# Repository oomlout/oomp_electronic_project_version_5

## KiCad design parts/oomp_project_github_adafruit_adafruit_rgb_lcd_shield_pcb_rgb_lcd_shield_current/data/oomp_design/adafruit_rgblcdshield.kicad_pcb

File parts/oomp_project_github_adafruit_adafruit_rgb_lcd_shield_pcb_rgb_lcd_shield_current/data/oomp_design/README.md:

# OOMP KiCad design copy

Open `adafruit_rgblcdshield.kicad_pro` (or the `.kicad_pcb` / `.kicad_sch`) in KiCad. Local OOMP libraries are under `libraries/`. Original inputs are preserved in [../original/](../original/).

Only verified unchanged installed KiCad defaults were renamed. Modified, custom, unmatched and unavailable items remain unchanged. Soldering variants are never swapped during conversion. Existing pad coordinates, nets and UUIDs are preserved.

See [conversion_report.yaml](conversion_report.yaml) for every conversion and skip. Copy this directory before editing; regeneration refuses to overwrite edited design files.

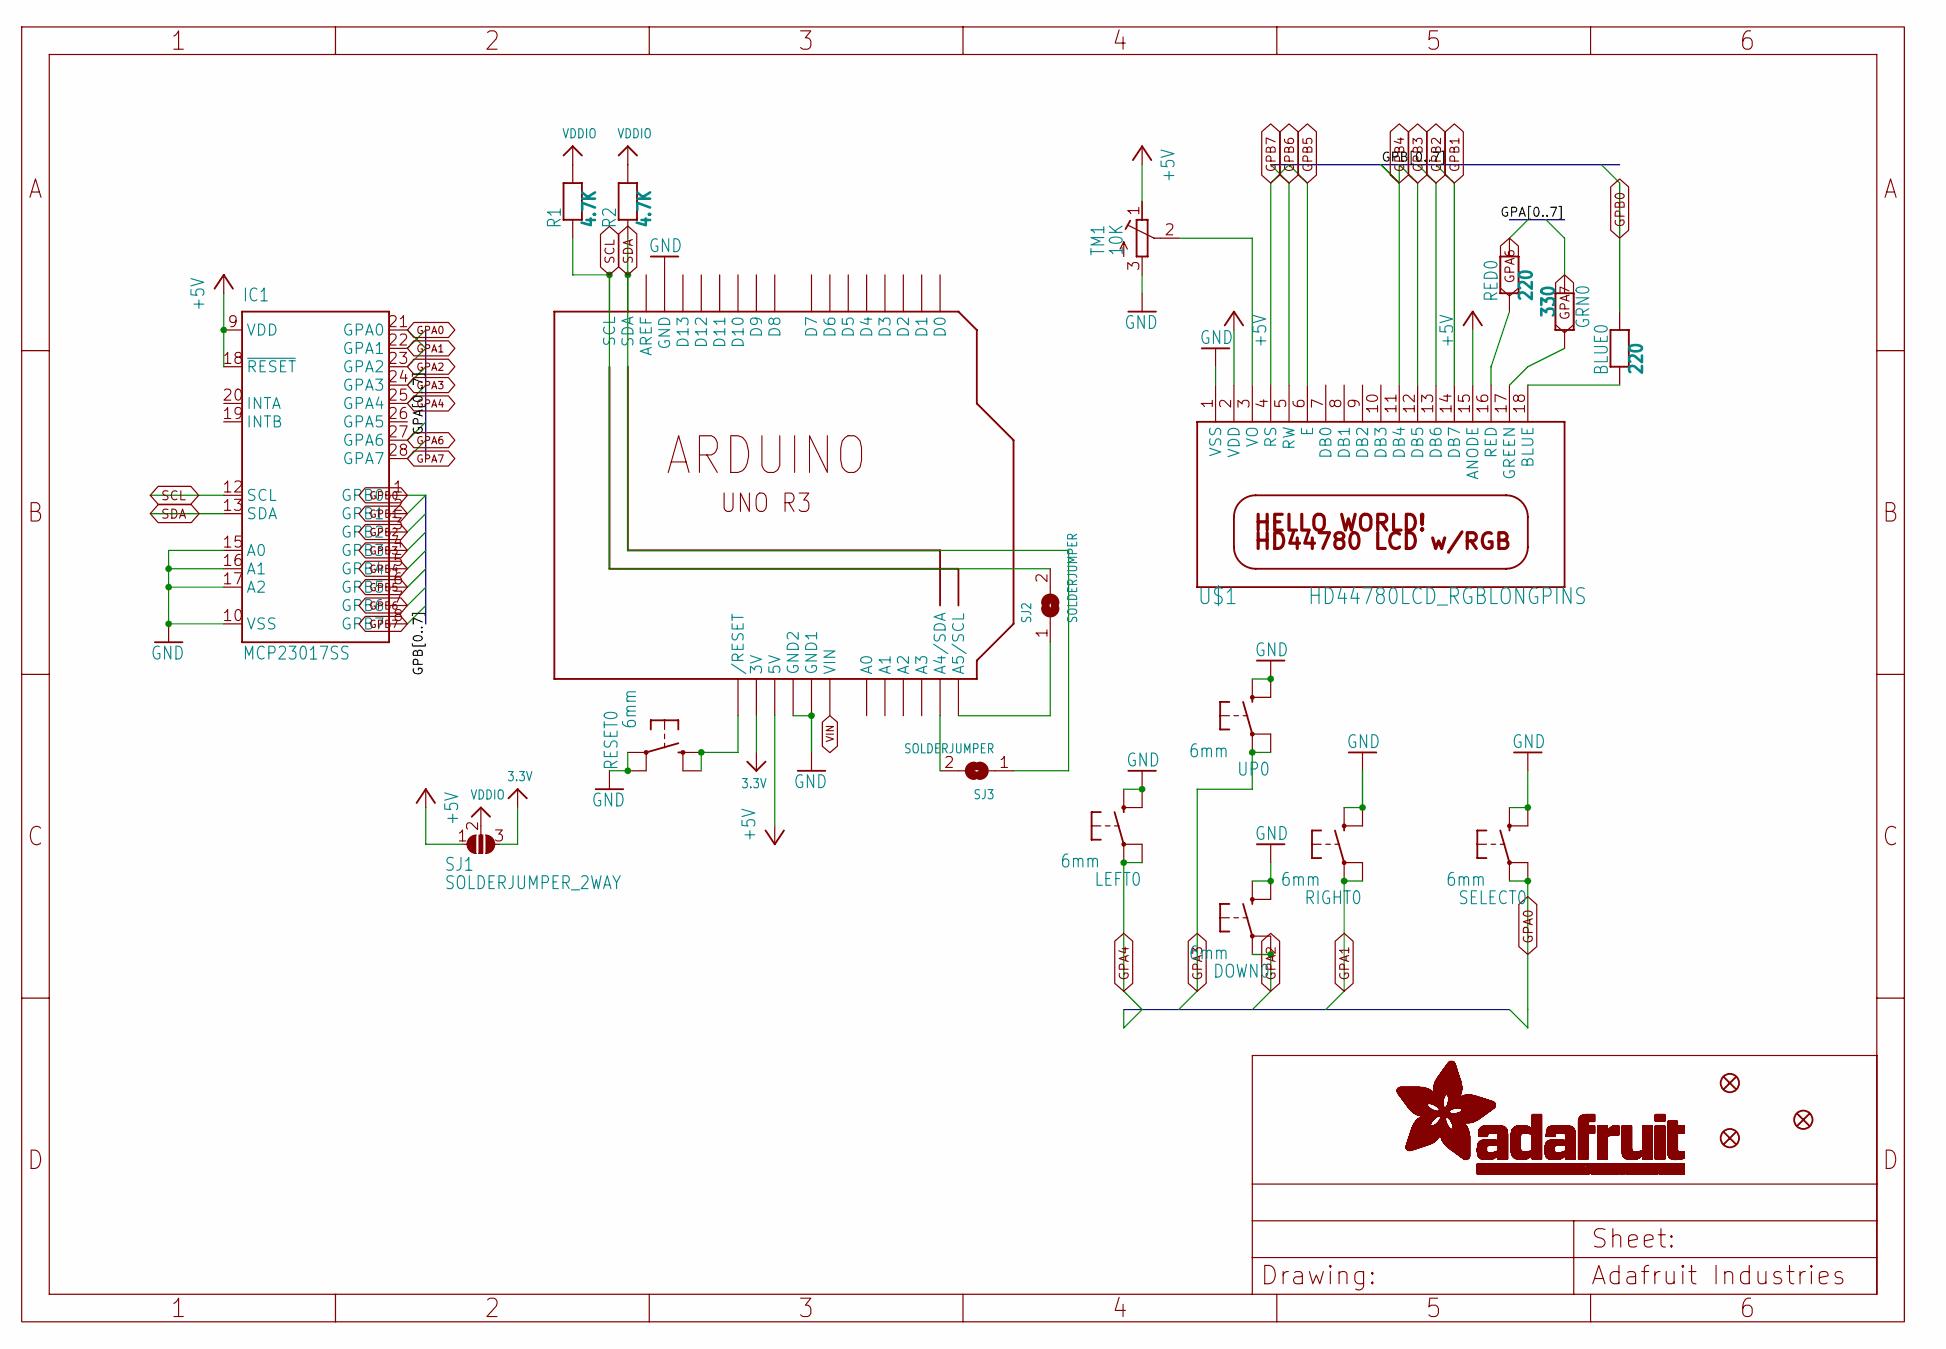
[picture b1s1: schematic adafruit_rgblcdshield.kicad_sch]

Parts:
BLUE0: 220; 0805-NO
DOWN0: 6mm; 6MMX6MM_TACTILE_SMT
FID1, FID2, FID3: FIDUCIAL_1MM
GRN0: 330; 0805-NO
IC1: MCP23017SS; SSOP28
LEFT0: 6mm; 6MMX6MM_TACTILE_SMT
R1, R2: 4.7K; 0805-NO
RED0: 220; 0805-NO
RESET0: 6mm; 6MMX6MM_TACTILE_SMT
RIGHT0: 6mm; 6MMX6MM_TACTILE_SMT
SELECT0: 6mm; 6MMX6MM_TACTILE_SMT
SJ1: SOLDERJUMPER_2WAY; SOLDERJUMPER_2WAY_OPEN_NOPASTE
SJ2, SJ3: SOLDERJUMPER; SOLDERJUMPER_ARROW_NOPASTE
TM1: 10K; RTRIM3314J
U1: ARDUINOR3-NOIOREF-NOTEXT; ARDUINOR3-NOTEXT-NOIOREF
U$1: HD44780LCD_RGBLONGPINS; LCD1602-RGB
UP0: 6mm; 6MMX6MM_TACTILE_SMT

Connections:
3.3V: SJ1.3, U1.3V
+5V: IC1.9 (VDD), IC1.18 (~RESET), SJ1.1, TM1.1 (E), U1.5V, U$1.2 (VDD), U$1.15 (ANODE)
GND: DOWN0.B (S), DOWN0.B' (S1), IC1.10 (VSS), IC1.15 (A0), IC1.16 (A1), IC1.17 (A2), LEFT0.B (S), LEFT0.B' (S1), RESET0.A, RESET0.A' (P1), RIGHT0.B (S), RIGHT0.B' (S1), SELECT0.B (S), SELECT0.B' (S1), TM1.3 (A), U1.GND, U1.GND1, U1.GND2, U$1.1 (VSS), UP0.B (S), UP0.B' (S1)
GPA0: IC1.21 (GPA0), SELECT0.A, SELECT0.A' (P1)
GPA1: IC1.22 (GPA1), RIGHT0.A, RIGHT0.A' (P1)
GPA2: DOWN0.A, DOWN0.A' (P1), IC1.23 (GPA2)
GPA3: IC1.24 (GPA3), UP0.A, UP0.A' (P1)
GPA4: IC1.25 (GPA4), LEFT0.A, LEFT0.A' (P1)
GPA6: IC1.27 (GPA6), RED0.2
GPA7: GRN0.1, IC1.28 (GPA7)
GPB0: BLUE0.2, IC1.1 (GPB0)
GPB1: IC1.2 (GPB1), U$1.14 (DB7)
GPB2: IC1.3 (GPB2), U$1.13 (DB6)
GPB3: IC1.4 (GPB3), U$1.12 (DB5)
GPB4: IC1.5 (GPB4), U$1.11 (DB4)
GPB5: IC1.6 (GPB5), U$1.6 (E)
GPB6: IC1.7 (GPB6), U$1.5 (RW)
GPB7: IC1.8 (GPB7), U$1.4 (RS)
unnamed: BLUE0.1, U$1.18 (BLUE)
unnamed: GRN0.2, U$1.17 (GREEN)
unnamed: RED0.1, U$1.16 (RED)
unnamed: TM1.2 (S), U$1.3 (VO)
unnamed: SJ3.2, U1.A4 (A4/SDA)
unnamed: SJ2.1, U1.A5 (A5/SCL)
RESET: RESET0.B (S), RESET0.B' (S1), U1.RESET (/RESET)
SCL: IC1.12 (SCL), R1.1, SJ2.2, U1.SCL
SDA: IC1.13 (SDA), R2.1, SJ3.1, U1.SDA
VDDIO: R1.2, R2.2, SJ1.2
VIN: U1.VIN

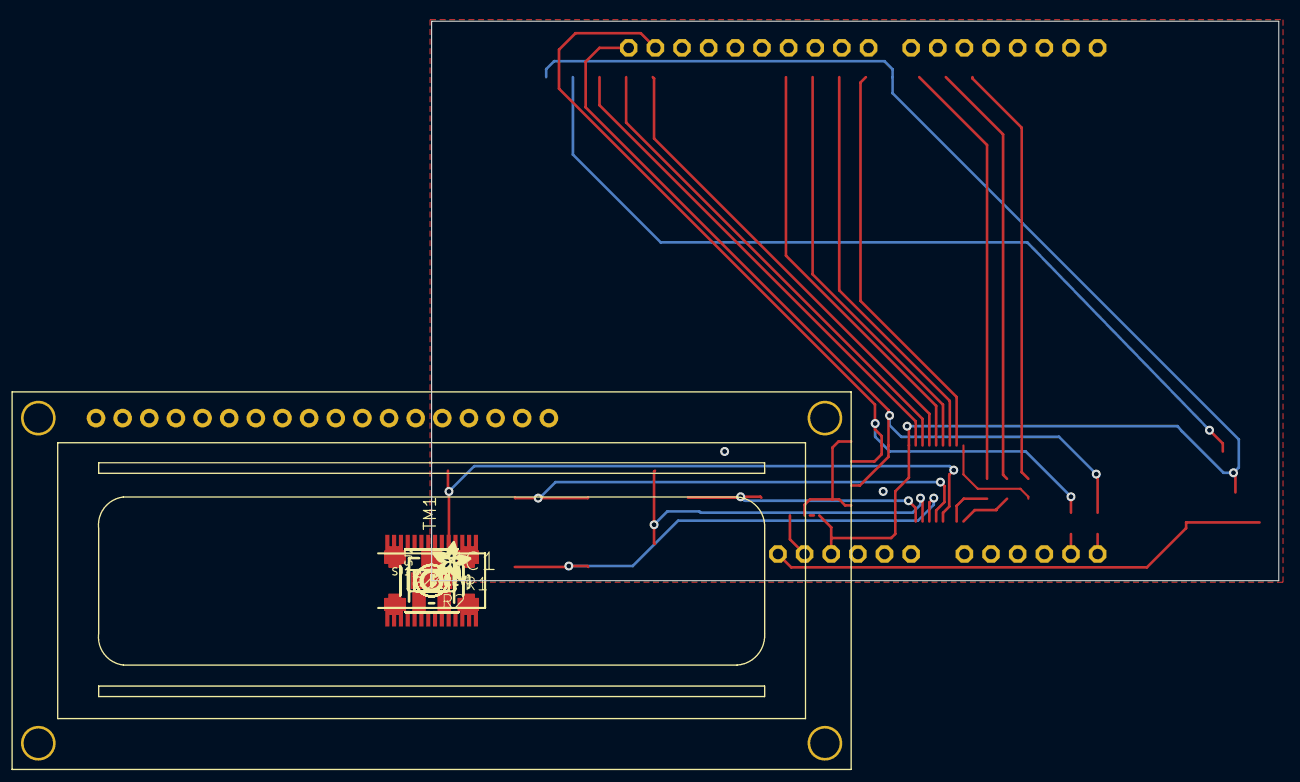
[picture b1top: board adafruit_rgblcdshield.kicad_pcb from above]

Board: 16 copper layers, 80.8 x 53.3 mm, 38 parts (0 on the bottom side), 28 nets.

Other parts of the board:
E$1: PCBFEAT-REV-040
PLABEL1: PLABEL1
PLABEL2: PLABEL2
PLABEL3: PLABEL3
PLABEL4: PLABEL4
PLABEL5: PLABEL5
PLABEL6: PLABEL6
PLABEL7: PLABEL7
PLABEL8: PLABEL8
PLABEL9: PLABEL9
PLABEL10: PLABEL10
PLABEL11: PLABEL11
PLABEL12: PLABEL12
PLABEL13: PLABEL13
PLABEL14: PLABEL14
PLABEL15: PLABEL15
U$4: ADAFRUIT_3.5MM

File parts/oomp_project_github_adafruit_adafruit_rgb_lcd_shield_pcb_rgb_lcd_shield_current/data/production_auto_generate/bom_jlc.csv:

Comment,Designator,Footprint,LCSC Part #
,U$4,adafruit_rgblcdshield-import-fps:ADAFRUIT_3.5MM,
,E$1,adafruit_rgblcdshield-import-fps:PCBFEAT-REV-040,
,PLABEL1,adafruit_rgblcdshield-import-fps:PLABEL1,
,PLABEL10,adafruit_rgblcdshield-import-fps:PLABEL10,
,PLABEL11,adafruit_rgblcdshield-import-fps:PLABEL11,
,PLABEL12,adafruit_rgblcdshield-import-fps:PLABEL12,
,PLABEL13,adafruit_rgblcdshield-import-fps:PLABEL13,
,PLABEL14,adafruit_rgblcdshield-import-fps:PLABEL14,
,PLABEL15,adafruit_rgblcdshield-import-fps:PLABEL15,
,PLABEL2,adafruit_rgblcdshield-import-fps:PLABEL2,
,PLABEL3,adafruit_rgblcdshield-import-fps:PLABEL3,
,PLABEL4,adafruit_rgblcdshield-import-fps:PLABEL4,
,PLABEL5,adafruit_rgblcdshield-import-fps:PLABEL5,
,PLABEL6,adafruit_rgblcdshield-import-fps:PLABEL6,
,PLABEL7,adafruit_rgblcdshield-import-fps:PLABEL7,
,PLABEL8,adafruit_rgblcdshield-import-fps:PLABEL8,
,PLABEL9,adafruit_rgblcdshield-import-fps:PLABEL9,
10K,TM1,adafruit_rgblcdshield-import-fps:RTRIM3314J,
220,BLUE0,adafruit_rgblcdshield-import-fps:0805-NO,
220,RED0,adafruit_rgblcdshield-import-fps:0805-NO,C2933369
330,GRN0,adafruit_rgblcdshield-import-fps:0805-NO,
4.7K,"R1,R2",adafruit_rgblcdshield-import-fps:0805-NO,C2907264
6mm,"DOWN0,LEFT0,RESET0,RIGHT0,SELECT0,UP0",adafruit_rgblcdshield-import-fps:6MMX6MM_TACTILE_SMT,
ARDUINOR3-NOIOREF-NOTEXT,U1,adafruit_rgblcdshield-import-fps:ARDUINOR3-NOTEXT-NOIOREF,
HD44780LCD_RGBLONGPINS,U$1,adafruit_rgblcdshield-import-fps:LCD1602-RGB,
MCP23017SS,IC1,adafruit_rgblcdshield-import-fps:SSOP28,

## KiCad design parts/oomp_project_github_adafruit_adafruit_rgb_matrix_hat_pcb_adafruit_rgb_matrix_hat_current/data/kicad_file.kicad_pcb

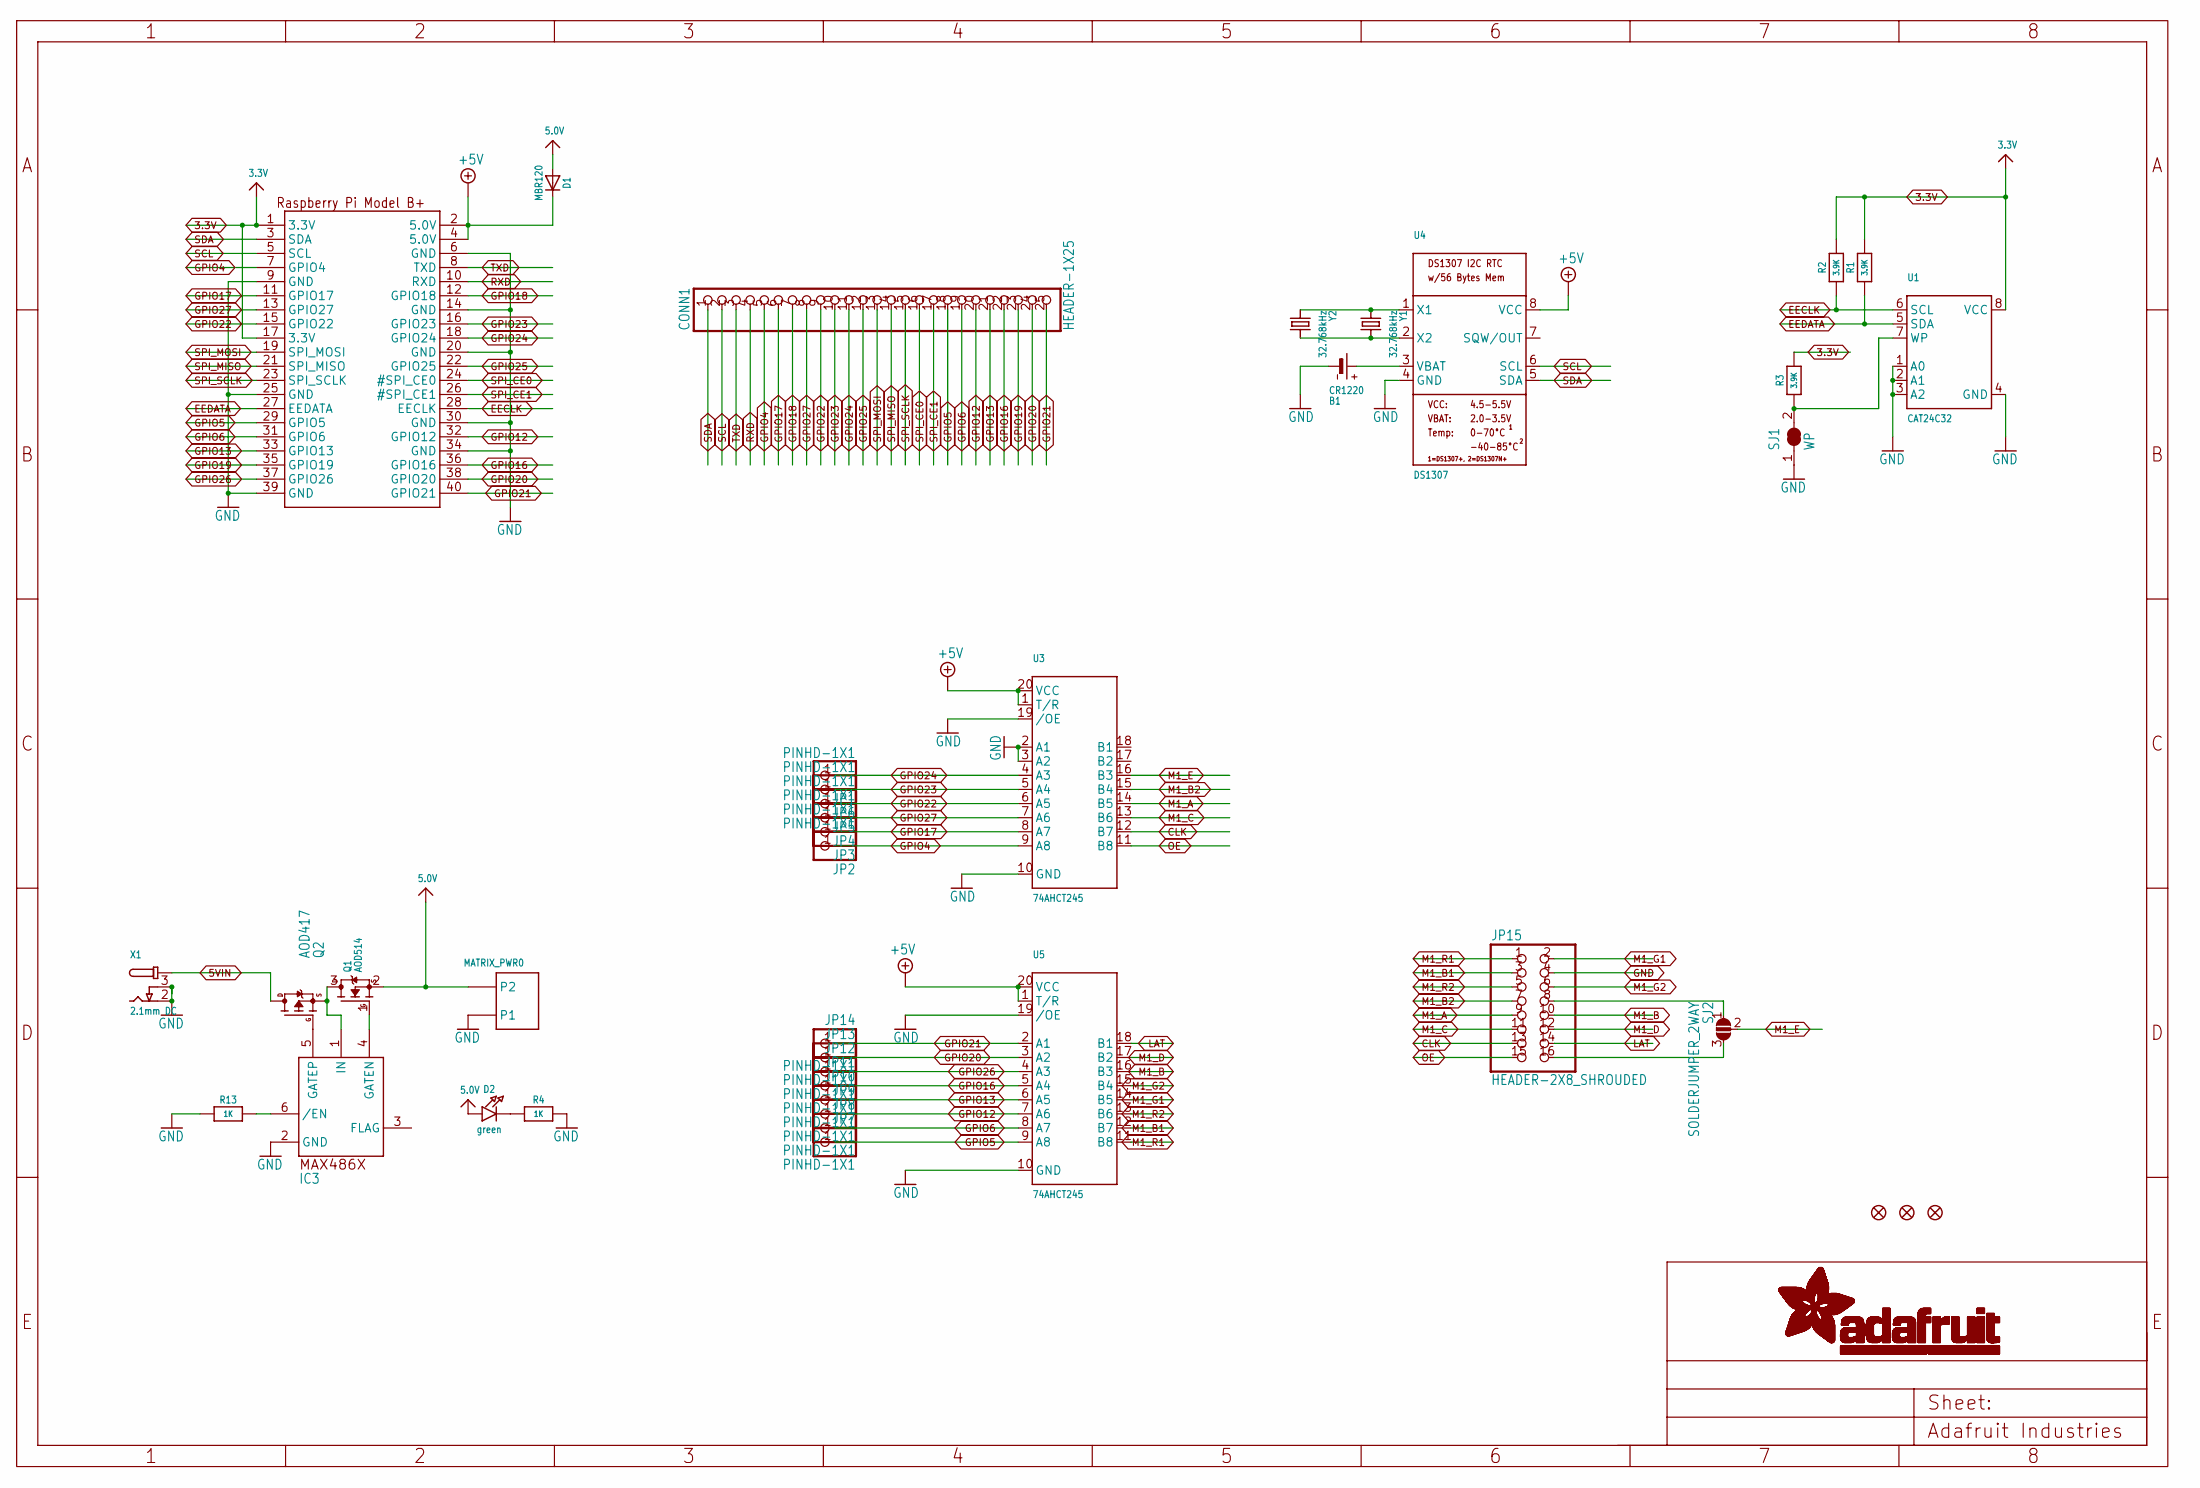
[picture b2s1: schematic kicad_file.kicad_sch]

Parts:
B1: CR1220
CONN1: HEADER-1X25; 1X25_ROUND_70MIL
D1: MBR120; SOD-123
D2: green; CHIPLED_0805_NOOUTLINE
FID1, FID2, FID3: FIDUCIAL_1MM
IC3: MAX4866T; SOT23-6
JP1, JP2, JP3, JP4, JP5, JP6, JP7, JP8, JP9, JP10, JP11, JP12, JP13, JP14: PINHD-1X1; 1X01
JP15: HEADER-2X8_SHROUDED; 2X08_SHROUDED
MATRIX_PWR0: PINHEAD; TERMBLOCK508
Q1: AOD514; TO252
Q2: AOD417; TO252
R1, R2, R3: 3.9K; 0805-NO
R4, R13: 1K; 0805-NO
RPI1: RASPBERRYPI_BPLUS_HATSLOTS; PI_HAT_SLOTS
SJ1: WP; SOLDERJUMPER_CLOSEDWIRE
SJ2: SOLDERJUMPER_2WAY; SOLDERJUMPER_2WAY_OPEN_NOPASTE
U1: CAT24C32; SOIC8_150MIL
U3, U5: 74AHCT245; TSSOP20
U4: DS1307; SOIC8_150MIL
X1: 2.1mm DC; DCJACK_2MM_SMT
Y1: 32.768kHz; CRYSTAL_8X3.8
Y2: 32.768kHz; XTAL3215

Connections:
3.3V: R1.2, R2.2, R3.2, RPI1.1 (3.3V), RPI1.17 (3.3V), U1.8 (VCC)
5.0V: D1.A, D2.A, MATRIX_PWR0.P$4 (P2), Q1.2 (S)
5VIN: Q2.3 (D), X1.1 (PWR), X1.1' (PWR)
+5V: D1.C, RPI1.2 (5.0V), RPI1.4 (5.0V), U3.1 (T/R), U3.20 (VCC), U4.8 (VCC), U5.1 (T/R), U5.20 (VCC)
CLK: JP15.13, U3.12 (B7)
EECLK: R2.1, RPI1.28 (EECLK), U1.6 (SCL)
EEDATA: R1.1, RPI1.27 (EEDATA), U1.5 (SDA)
GND: B1.-, IC3.2 (GND), JP15.4, MATRIX_PWR0.P$3 (P1), R4.2, R13.1, RPI1.6 (GND), RPI1.9 (GND), RPI1.14 (GND), RPI1.20 (GND), RPI1.25 (GND), RPI1.30 (GND), RPI1.34 (GND), RPI1.39 (GND), SJ1.1, U1.1 (A0), U1.2 (A1), U1.3 (A2), U1.4 (GND), U3.2 (A1), U3.3 (A2), U3.10 (GND), U3.19 (/OE), U4.4 (GND), U5.10 (GND), U5.19 (/OE), X1.2 (GND), X1.3 (GNDBREAK)
GPIO4: CONN1.5, JP2.1, RPI1.7 (GPIO4), U3.9 (A8)
GPIO5: CONN1.18, JP7.1, RPI1.29 (GPIO5), U5.9 (A8)
GPIO6: CONN1.19, JP8.1, RPI1.31 (GPIO6), U5.8 (A7)
GPIO12: CONN1.20, JP9.1, RPI1.32 (GPIO12), U5.7 (A6)
GPIO13: CONN1.21, JP10.1, RPI1.33 (GPIO13), U5.6 (A5)
GPIO16: CONN1.22, JP11.1, RPI1.36 (GPIO16), U5.5 (A4)
GPIO17: CONN1.6, JP3.1, RPI1.11 (GPIO17), U3.8 (A7)
GPIO18: CONN1.7, RPI1.12 (GPIO18)
GPIO19: CONN1.23, RPI1.35 (GPIO19)
GPIO20: CONN1.24, JP13.1, RPI1.38 (GPIO20), U5.3 (A2)
GPIO21: CONN1.25, JP14.1, RPI1.40 (GPIO21), U5.2 (A1)
GPIO22: CONN1.9, JP5.1, RPI1.15 (GPIO22), U3.6 (A5)
GPIO23: CONN1.10, JP6.1, RPI1.16 (GPIO23), U3.5 (A4)
GPIO24: CONN1.11, JP1.1, RPI1.18 (GPIO24), U3.4 (A3)
GPIO25: CONN1.12, RPI1.22 (GPIO25)
GPIO26: JP12.1, RPI1.37 (GPIO26), U5.4 (A3)
GPIO27: CONN1.8, JP4.1, RPI1.13 (GPIO27), U3.7 (A6)
LAT: JP15.14, U5.18 (B1)
M1_A: JP15.9, U3.14 (B5)
M1_B: JP15.10, U5.16 (B3)
M1_B1: JP15.3, U5.12 (B7)
M1_B2: JP15.7, U3.15 (B4)
M1_C: JP15.11, U3.13 (B6)
M1_D: JP15.12, U5.17 (B2)
M1_E: SJ2.2, U3.16 (B3)
M1_E': JP15.8, SJ2.1
M1_E'': JP15.16, SJ2.3
M1_G1: JP15.2, U5.14 (B5)
M1_G2: JP15.6, U5.15 (B4)
M1_R1: JP15.1, U5.11 (B8)
M1_R2: JP15.5, U5.13 (B6)
unnamed: IC3.6 (/EN), R13.2
unnamed: U4.1 (X1), Y1.P$1 (1), Y2.P$1 (1)
unnamed: U4.2 (X2), Y1.P$4 (2), Y2.P$2 (2)
unnamed: D2.C, R4.1
unnamed: IC3.1 (IN), Q1.3 (D), Q2.2 (S)
unnamed: IC3.4 (GATEN), Q1.1 (G)
unnamed: IC3.5 (GATEP), Q2.1 (G)
unnamed: B1.+$1 (+), B1.+$2 (+), U4.3 (VBAT)
unnamed: R3.1, SJ1.2, U1.7 (WP)
OE: JP15.15, U3.11 (B8)
RXD: CONN1.4, RPI1.10 (RXD)
SCL: CONN1.2, RPI1.5 (SCL), U4.6 (SCL)
SDA: CONN1.1, RPI1.3 (SDA), U4.5 (SDA)
SPI_CE0: CONN1.16, RPI1.24 (#SPI_CE0)
SPI_CE1: CONN1.17, RPI1.26 (#SPI_CE1)
SPI_MISO: CONN1.14, RPI1.21 (SPI_MISO)
SPI_MOSI: CONN1.13, RPI1.19 (SPI_MOSI)
SPI_SCLK: CONN1.15, RPI1.23 (SPI_SCLK)
TXD: CONN1.3, RPI1.8 (TXD)

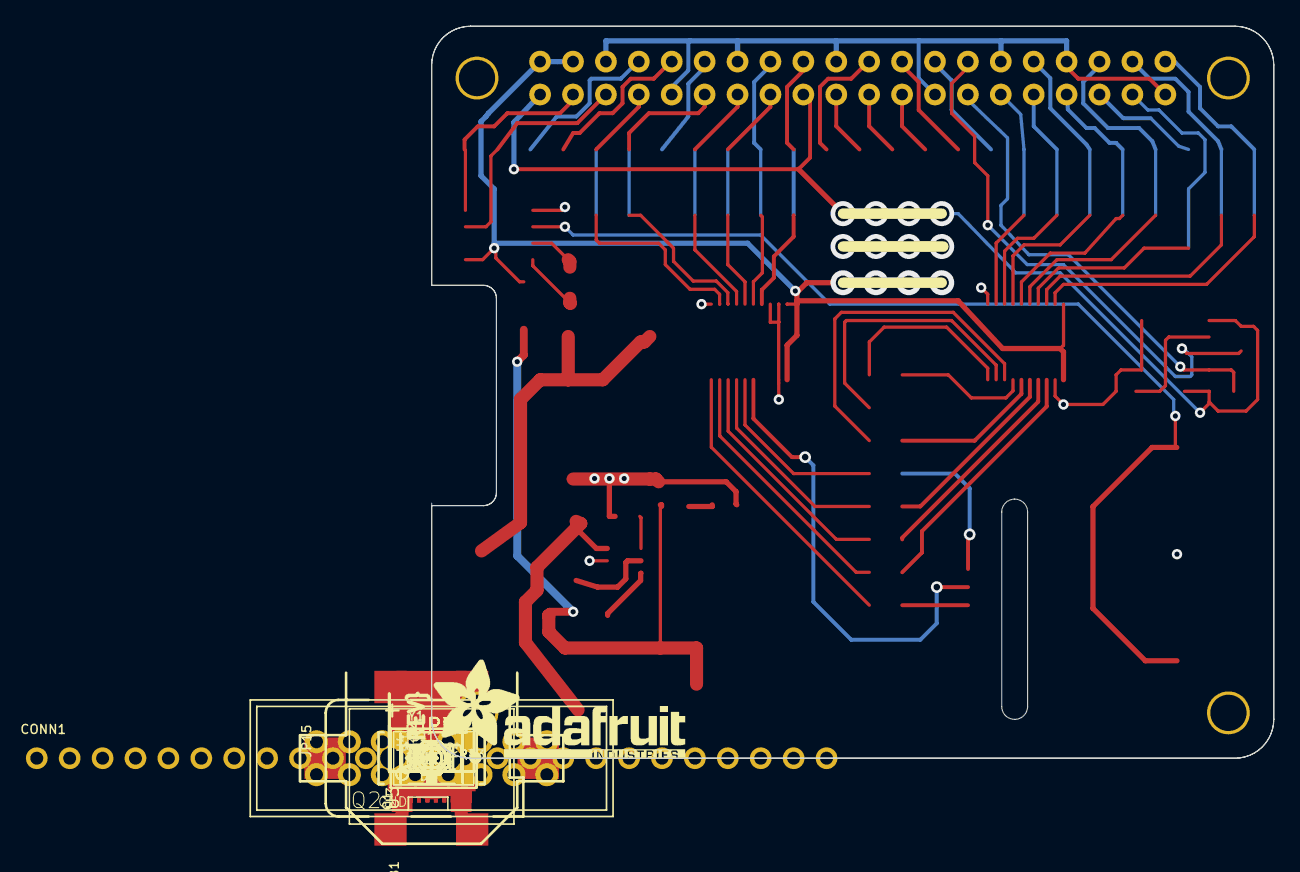
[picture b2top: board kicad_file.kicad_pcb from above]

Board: 2 copper layers, 65.0 x 56.5 mm, 97 parts (0 on the bottom side), 58 nets.

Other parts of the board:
PLABEL0: PLABEL0
PLABEL1: PLABEL1
PLABEL2: PLABEL2
PLABEL3: PLABEL3
PLABEL4: PLABEL4
PLABEL5: PLABEL5
PLABEL6: PLABEL6
PLABEL7: PLABEL7
PLABEL8: PLABEL8
PLABEL9: PLABEL9
PLABEL10: PLABEL10
PLABEL11: PLABEL11
PLABEL12: PLABEL12
PLABEL13: PLABEL13
PLABEL14: PLABEL14
PLABEL15: PLABEL15
PLABEL16: PLABEL16
PLABEL17: PLABEL17
PLABEL18: PLABEL18
PLABEL19: PLABEL19
PLABEL20: PLABEL20
PLABEL21: PLABEL21
PLABEL22: PLABEL22
PLABEL23: PLABEL23
PLABEL24: PLABEL24
PLABEL25: PLABEL25
PLABEL26: PLABEL26
PLABEL27: PLABEL27
PLABEL28: PLABEL28
PLABEL29: PLABEL29
PLABEL30: PLABEL30
PLABEL31: PLABEL31
PLABEL32: PLABEL32
PLABEL33: PLABEL33
PLABEL34: PLABEL34
PLABEL35: PLABEL35
PLABEL36: PLABEL36
PLABEL37: PLABEL37
PLABEL38: PLABEL38
PLABEL39: PLABEL39
PLABEL40: PLABEL40
PLABEL41: PLABEL41
PLABEL42: PLABEL42
PLABEL43: PLABEL43
PLABEL44: PLABEL44
PLABEL45: PLABEL45
PLABEL46: PLABEL46
PLABEL47: PLABEL47
PLABEL48: PLABEL48
PLABEL49: PLABEL49
PLABEL50: PLABEL50
PLABEL51: PLABEL51
U$3: PCBFEAT-REV-056
U$10: SYMBOL_PLUS
U$11: SYMBOL_MINUS
U$12: ADAFRUIT_TEXT_20MM

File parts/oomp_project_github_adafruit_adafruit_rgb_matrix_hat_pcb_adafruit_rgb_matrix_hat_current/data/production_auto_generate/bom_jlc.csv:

Comment,Designator,Footprint,LCSC Part #
,"JP1,JP2,JP3,JP4,JP5,JP6,JP7,JP8,JP9,JP10,JP11,JP12,JP13,JP14",Adafruit RGB Matrix HAT-import-fps:1X01,C7501259
,JP15,Adafruit RGB Matrix HAT-import-fps:2X08_SHROUDED,
,U$12,Adafruit RGB Matrix HAT-import-fps:ADAFRUIT_TEXT_20MM,
,U$3,Adafruit RGB Matrix HAT-import-fps:PCBFEAT-REV-056,
,PLABEL0,Adafruit RGB Matrix HAT-import-fps:PLABEL0,
,PLABEL1,Adafruit RGB Matrix HAT-import-fps:PLABEL1,
,PLABEL10,Adafruit RGB Matrix HAT-import-fps:PLABEL10,
,PLABEL11,Adafruit RGB Matrix HAT-import-fps:PLABEL11,
,PLABEL12,Adafruit RGB Matrix HAT-import-fps:PLABEL12,
,PLABEL13,Adafruit RGB Matrix HAT-import-fps:PLABEL13,
,PLABEL14,Adafruit RGB Matrix HAT-import-fps:PLABEL14,
,PLABEL15,Adafruit RGB Matrix HAT-import-fps:PLABEL15,
,PLABEL16,Adafruit RGB Matrix HAT-import-fps:PLABEL16,
,PLABEL17,Adafruit RGB Matrix HAT-import-fps:PLABEL17,
,PLABEL18,Adafruit RGB Matrix HAT-import-fps:PLABEL18,
,PLABEL19,Adafruit RGB Matrix HAT-import-fps:PLABEL19,
,PLABEL2,Adafruit RGB Matrix HAT-import-fps:PLABEL2,
,PLABEL20,Adafruit RGB Matrix HAT-import-fps:PLABEL20,
,PLABEL21,Adafruit RGB Matrix HAT-import-fps:PLABEL21,
,PLABEL22,Adafruit RGB Matrix HAT-import-fps:PLABEL22,
,PLABEL23,Adafruit RGB Matrix HAT-import-fps:PLABEL23,
,PLABEL24,Adafruit RGB Matrix HAT-import-fps:PLABEL24,
,PLABEL25,Adafruit RGB Matrix HAT-import-fps:PLABEL25,
,PLABEL26,Adafruit RGB Matrix HAT-import-fps:PLABEL26,
,PLABEL27,Adafruit RGB Matrix HAT-import-fps:PLABEL27,
,PLABEL28,Adafruit RGB Matrix HAT-import-fps:PLABEL28,
,PLABEL29,Adafruit RGB Matrix HAT-import-fps:PLABEL29,
,PLABEL3,Adafruit RGB Matrix HAT-import-fps:PLABEL3,
,PLABEL30,Adafruit RGB Matrix HAT-import-fps:PLABEL30,
,PLABEL31,Adafruit RGB Matrix HAT-import-fps:PLABEL31,
,PLABEL32,Adafruit RGB Matrix HAT-import-fps:PLABEL32,
,PLABEL33,Adafruit RGB Matrix HAT-import-fps:PLABEL33,
,PLABEL34,Adafruit RGB Matrix HAT-import-fps:PLABEL34,
,PLABEL35,Adafruit RGB Matrix HAT-import-fps:PLABEL35,
,PLABEL36,Adafruit RGB Matrix HAT-import-fps:PLABEL36,
,PLABEL37,Adafruit RGB Matrix HAT-import-fps:PLABEL37,
,PLABEL38,Adafruit RGB Matrix HAT-import-fps:PLABEL38,
,PLABEL39,Adafruit RGB Matrix HAT-import-fps:PLABEL39,
,PLABEL4,Adafruit RGB Matrix HAT-import-fps:PLABEL4,
,PLABEL40,Adafruit RGB Matrix HAT-import-fps:PLABEL40,
,PLABEL41,Adafruit RGB Matrix HAT-import-fps:PLABEL41,
,PLABEL42,Adafruit RGB Matrix HAT-import-fps:PLABEL42,
,PLABEL43,Adafruit RGB Matrix HAT-import-fps:PLABEL43,
,PLABEL44,Adafruit RGB Matrix HAT-import-fps:PLABEL44,
,PLABEL45,Adafruit RGB Matrix HAT-import-fps:PLABEL45,
,PLABEL46,Adafruit RGB Matrix HAT-import-fps:PLABEL46,
,PLABEL47,Adafruit RGB Matrix HAT-import-fps:PLABEL47,
,PLABEL48,Adafruit RGB Matrix HAT-import-fps:PLABEL48,
,PLABEL49,Adafruit RGB Matrix HAT-import-fps:PLABEL49,
,PLABEL5,Adafruit RGB Matrix HAT-import-fps:PLABEL5,
,PLABEL50,Adafruit RGB Matrix HAT-import-fps:PLABEL50,
,PLABEL51,Adafruit RGB Matrix HAT-import-fps:PLABEL51,
,PLABEL6,Adafruit RGB Matrix HAT-import-fps:PLABEL6,
,PLABEL7,Adafruit RGB Matrix HAT-import-fps:PLABEL7,
,PLABEL8,Adafruit RGB Matrix HAT-import-fps:PLABEL8,
,PLABEL9,Adafruit RGB Matrix HAT-import-fps:PLABEL9,
,U$11,Adafruit RGB Matrix HAT-import-fps:SYMBOL_MINUS,
,U$10,Adafruit RGB Matrix HAT-import-fps:SYMBOL_PLUS,
1K,"R4,R13",Adafruit RGB Matrix HAT-import-fps:0805-NO,C17513
2.1mm DC,X1,Adafruit RGB Matrix HAT-import-fps:DCJACK_2MM_SMT,
3.9K,"R1,R2,R3",Adafruit RGB Matrix HAT-import-fps:0805-NO,C2907252
32.768kHz,Y1,Adafruit RGB Matrix HAT-import-fps:CRYSTAL_8X3.8,
32.768kHz,Y2,Adafruit RGB Matrix HAT-import-fps:XTAL3215,
74AHCT245,"U3,U5",Adafruit RGB Matrix HAT-import-fps:TSSOP20,
AOD417,Q2,Adafruit RGB Matrix HAT-import-fps:TO252,
AOD514,Q1,Adafruit RGB Matrix HAT-import-fps:TO252,
CAT24C32,U1,Adafruit RGB Matrix HAT-import-fps:SOIC8_150MIL,
CR1220,B1,Adafruit RGB Matrix HAT-import-fps:CR1220,
DS1307,U4,Adafruit RGB Matrix HAT-import-fps:SOIC8_150MIL,
green,D2,Adafruit RGB Matrix HAT-import-fps:CHIPLED_0805_NOOUTLINE,
HEADER-1X25,CONN1,Adafruit RGB Matrix HAT-import-fps:1X25_ROUND_70MIL,C2883713
MAX4866T,IC3,Adafruit RGB Matrix HAT-import-fps:SOT23-6,
MBR120,D1,Adafruit RGB Matrix HAT-import-fps:SOD-123,
RASPBERRYPI_BPLUS_HATSLOTS,RPI1,Adafruit RGB Matrix HAT-import-fps:PI_HAT_SLOTS,

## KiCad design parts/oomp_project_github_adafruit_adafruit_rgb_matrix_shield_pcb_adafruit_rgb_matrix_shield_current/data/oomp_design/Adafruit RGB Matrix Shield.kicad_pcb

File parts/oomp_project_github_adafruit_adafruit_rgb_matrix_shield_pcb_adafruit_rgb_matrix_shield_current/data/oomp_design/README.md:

# OOMP KiCad design copy

Open `Adafruit RGB Matrix Shield.kicad_pro` (or the `.kicad_pcb` / `.kicad_sch`) in KiCad. Local OOMP libraries are under `libraries/`. Original inputs are preserved in [../original/](../original/).

Only verified unchanged installed KiCad defaults were renamed. Modified, custom, unmatched and unavailable items remain unchanged. Soldering variants are never swapped during conversion. Existing pad coordinates, nets and UUIDs are preserved.

See [conversion_report.yaml](conversion_report.yaml) for every conversion and skip. Copy this directory before editing; regeneration refuses to overwrite edited design files.

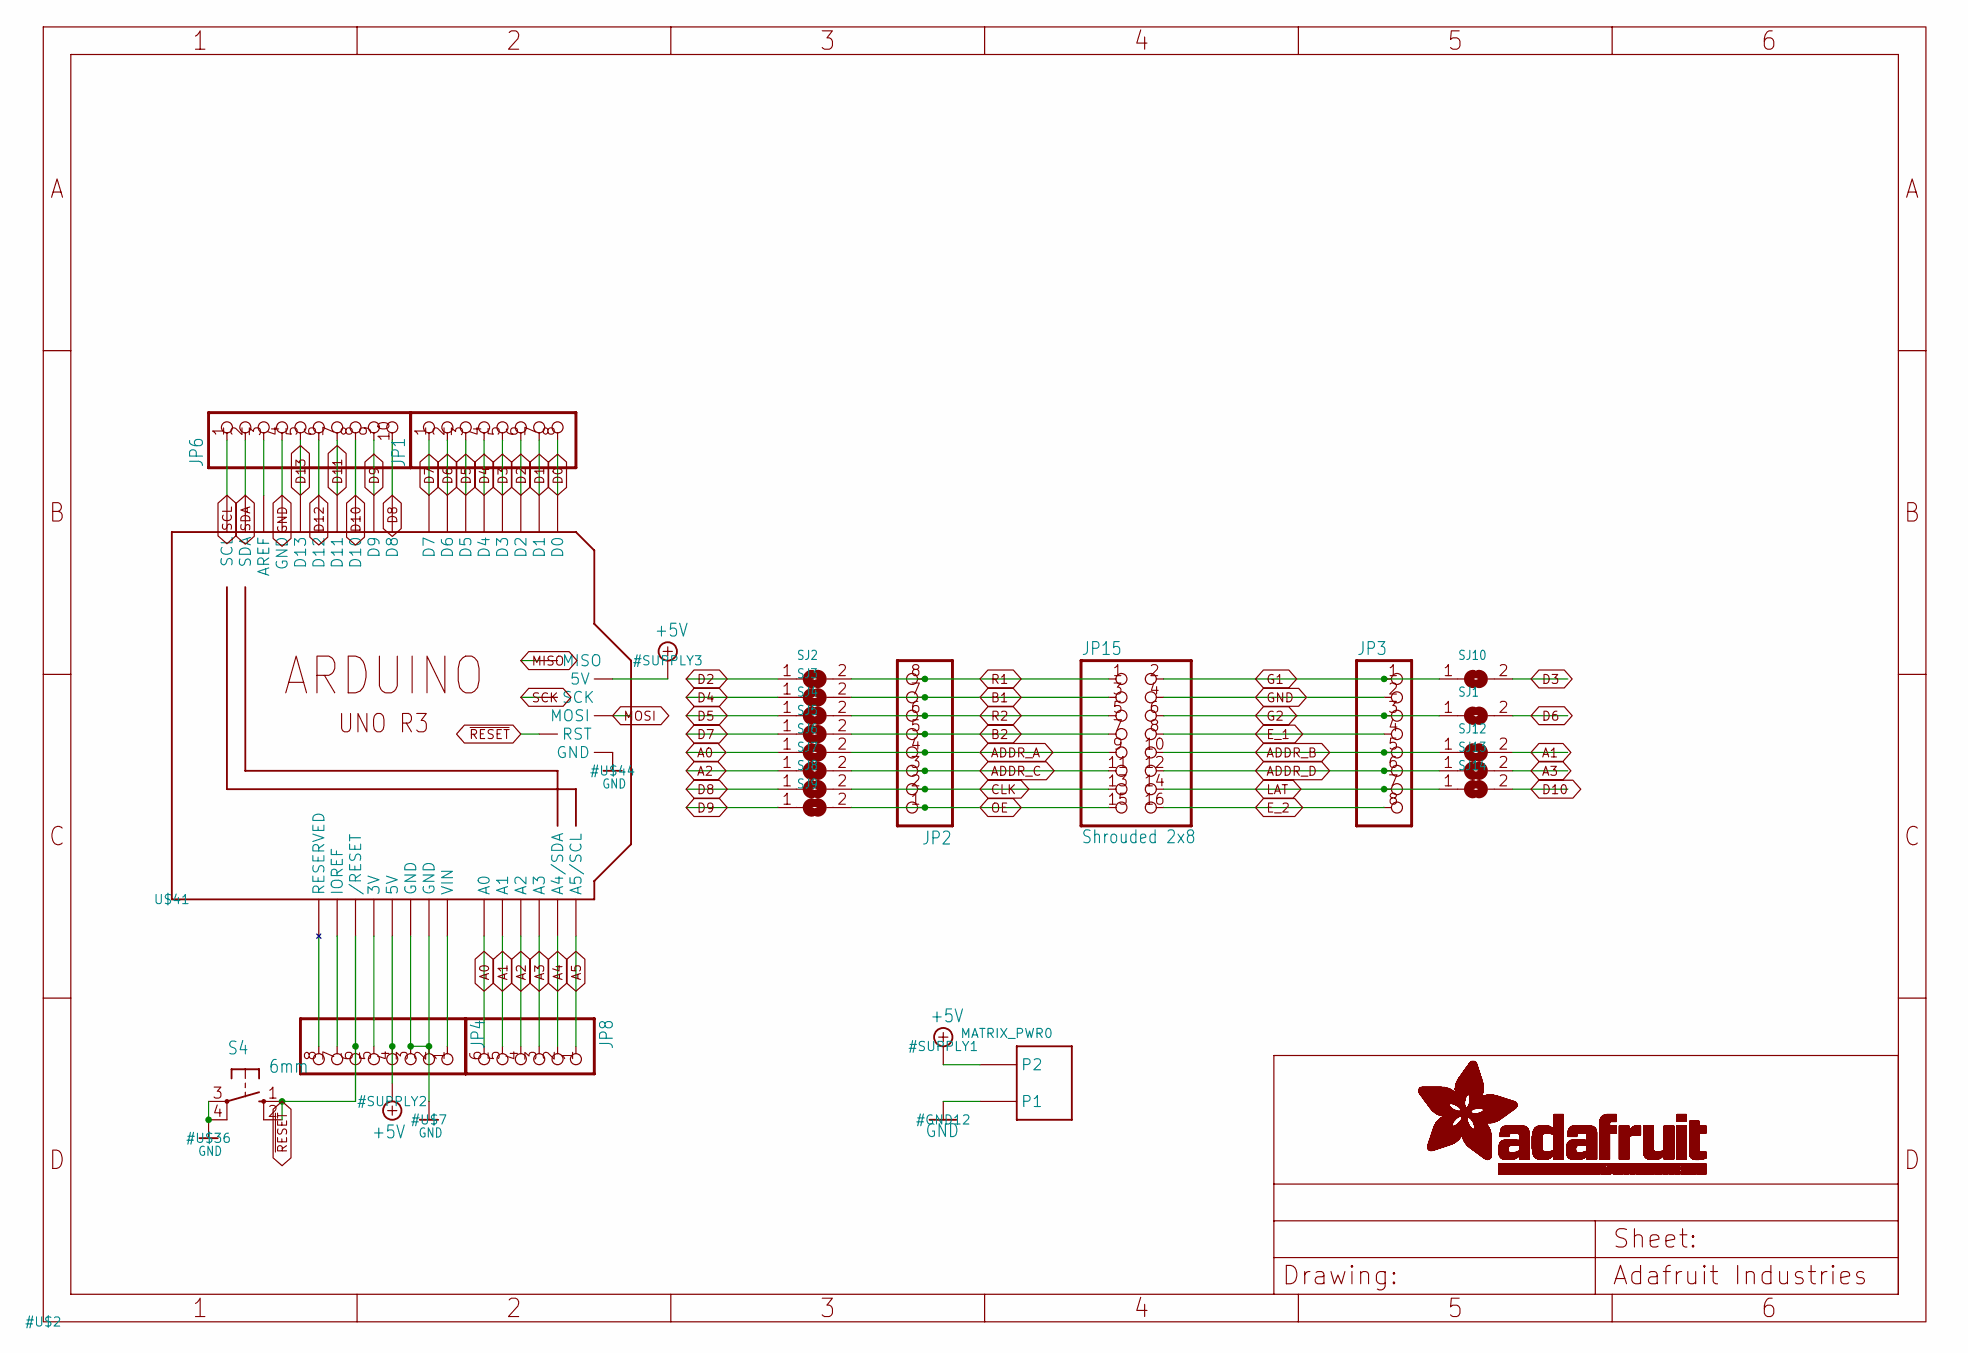
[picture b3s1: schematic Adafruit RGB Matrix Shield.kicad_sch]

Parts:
JP1, JP4: PINHD-1X8CLEANBIG; 1X08-CLEANBIG
JP2, JP3: HEADER-1X876MIL; 1X08_ROUND_76
JP6: HEADER-1X1070MIL; 1X10_ROUND70
JP8: PINHD-1X6CB; 1X06-CLEANBIG
JP15: Shrouded 2x8; 2X08_SHROUDED
MATRIX_PWR0: PINHEAD; TERMBLOCK508
S4: 6mm; B3F-10XX; MPN B3F-1000
SJ1, SJ2, SJ3, SJ4, SJ5, SJ6, SJ7, SJ8, SJ9, SJ10, SJ12, SJ13, SJ14: SOLDERJUMPERCLOSED; SOLDERJUMPER_CLOSEDWIRE
U$41: ARDUINO_R3_ICSP_NODIM; ARDUINOR3_ICSP_NODIM

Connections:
+3V: JP4.5, U$41.3V
+5V: JP4.4, MATRIX_PWR0.P$4 (P2), U$41.5V, U$41.5V_ICSP (5V)
A0: JP8.6, SJ6.1, U$41.A0
A1: JP8.5, SJ12.2, U$41.A1
A2: JP8.4, SJ7.1, U$41.A2
A3: JP8.3, SJ13.2, U$41.A3
A4: JP8.2, U$41.A4 (A4/SDA)
A5: JP8.1, U$41.A5 (A5/SCL)
ADDR_A: JP2.4, JP15.9, SJ6.2
ADDR_B: JP3.5, JP15.10, SJ12.1
ADDR_C: JP2.3, JP15.11, SJ7.2
ADDR_D: JP3.6, JP15.12, SJ13.1
AREF: JP6.3, U$41.AREF
B1: JP2.7, JP15.3, SJ3.2
B2: JP2.5, JP15.7, SJ5.2
CLK: JP2.2, JP15.13, SJ8.2
D0: JP1.8, U$41.D0
D1: JP1.7, U$41.D1
D2: JP1.6, SJ2.1, U$41.D2
D3: JP1.5, SJ10.2, U$41.D3
D4: JP1.4, SJ3.1, U$41.D4
D5: JP1.3, SJ4.1, U$41.D5
D6: JP1.2, SJ1.2, U$41.D6
D7: JP1.1, SJ5.1, U$41.D7
D8: JP6.10, SJ8.1, U$41.D8
D9: JP6.9, SJ9.1, U$41.D9
D10: JP6.8, SJ14.2, U$41.D10
D11: JP6.7, U$41.D11
D12: JP6.6, U$41.D12
D13: JP6.5, U$41.D13
E_1: JP3.4, JP15.8
E_2: JP3.8, JP15.16
G1: JP3.1, JP15.2, SJ10.1
G2: JP3.3, JP15.6, SJ1.1
GND: JP3.2, JP4.2, JP4.3, JP6.4, JP15.4, MATRIX_PWR0.P$3 (P1), S4.3, S4.4 (P1), U$41.GND, U$41.GND@1 (GND), U$41.GND@2 (GND), U$41.GND@3 (GND)
IOREF: JP4.7, U$41.IOREF
LAT: JP3.7, JP15.14, SJ14.1
MISO: U$41.MISO
MOSI: U$41.MOSI
NC: JP4.8, U$41.RESERVED
OE: JP2.1, JP15.15, SJ9.2
R1: JP2.8, JP15.1, SJ2.2
R2: JP2.6, JP15.5, SJ4.2
SCK: U$41.SCK
SCL: JP6.1, U$41.SCL
SDA: JP6.2, U$41.SDA
VIN: JP4.1, U$41.VIN
~RESET: JP4.6, S4.1 (S), S4.2 (S1), U$41.RESET (/RESET), U$41.RESET_ICSP (RST)

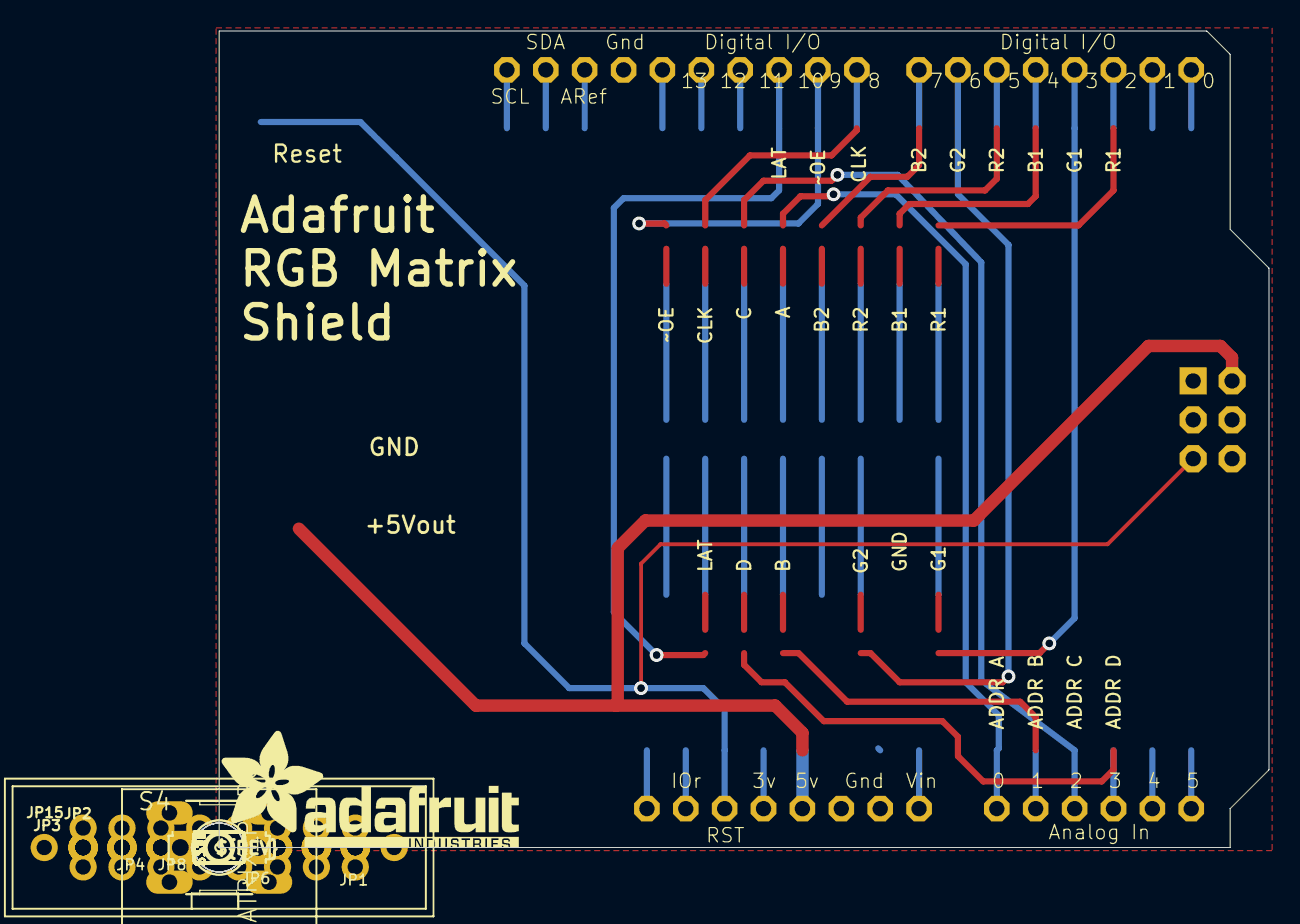
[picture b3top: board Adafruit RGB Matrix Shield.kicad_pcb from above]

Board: 2 copper layers, 68.6 x 53.3 mm, 28 parts (0 on the bottom side), 45 nets.

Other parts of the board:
U$8: PCBFEAT-REV-040
U$9: ADAFRUIT_TEXT_20MM
UNK_HOLE_0: dummyfp0
UNK_HOLE_1: dummyfp1
UNK_HOLE_2: dummyfp2

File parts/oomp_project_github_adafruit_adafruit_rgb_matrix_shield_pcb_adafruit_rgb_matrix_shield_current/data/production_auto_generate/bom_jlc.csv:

Comment,Designator,Footprint,LCSC Part #
,JP8,Adafruit RGB Matrix Shield-import-fps:1X06-CLEANBIG,C37208
,"JP1,JP4",Adafruit RGB Matrix Shield-import-fps:1X08-CLEANBIG,C492421
,"JP2,JP3",Adafruit RGB Matrix Shield-import-fps:1X08_ROUND_76,C492421
,JP6,Adafruit RGB Matrix Shield-import-fps:1X10_ROUND70,C57369
,U$9,Adafruit RGB Matrix Shield-import-fps:ADAFRUIT_TEXT_20MM,
,U$8,Adafruit RGB Matrix Shield-import-fps:PCBFEAT-REV-040,
6mm,S4,Adafruit RGB Matrix Shield-import-fps:B3F-10XX,
ARDUINO_R3_ICSP_NODIM,U$41,Adafruit RGB Matrix Shield-import-fps:ARDUINOR3_ICSP_NODIM,
Shrouded 2x8,JP15,Adafruit RGB Matrix Shield-import-fps:2X08_SHROUDED,
